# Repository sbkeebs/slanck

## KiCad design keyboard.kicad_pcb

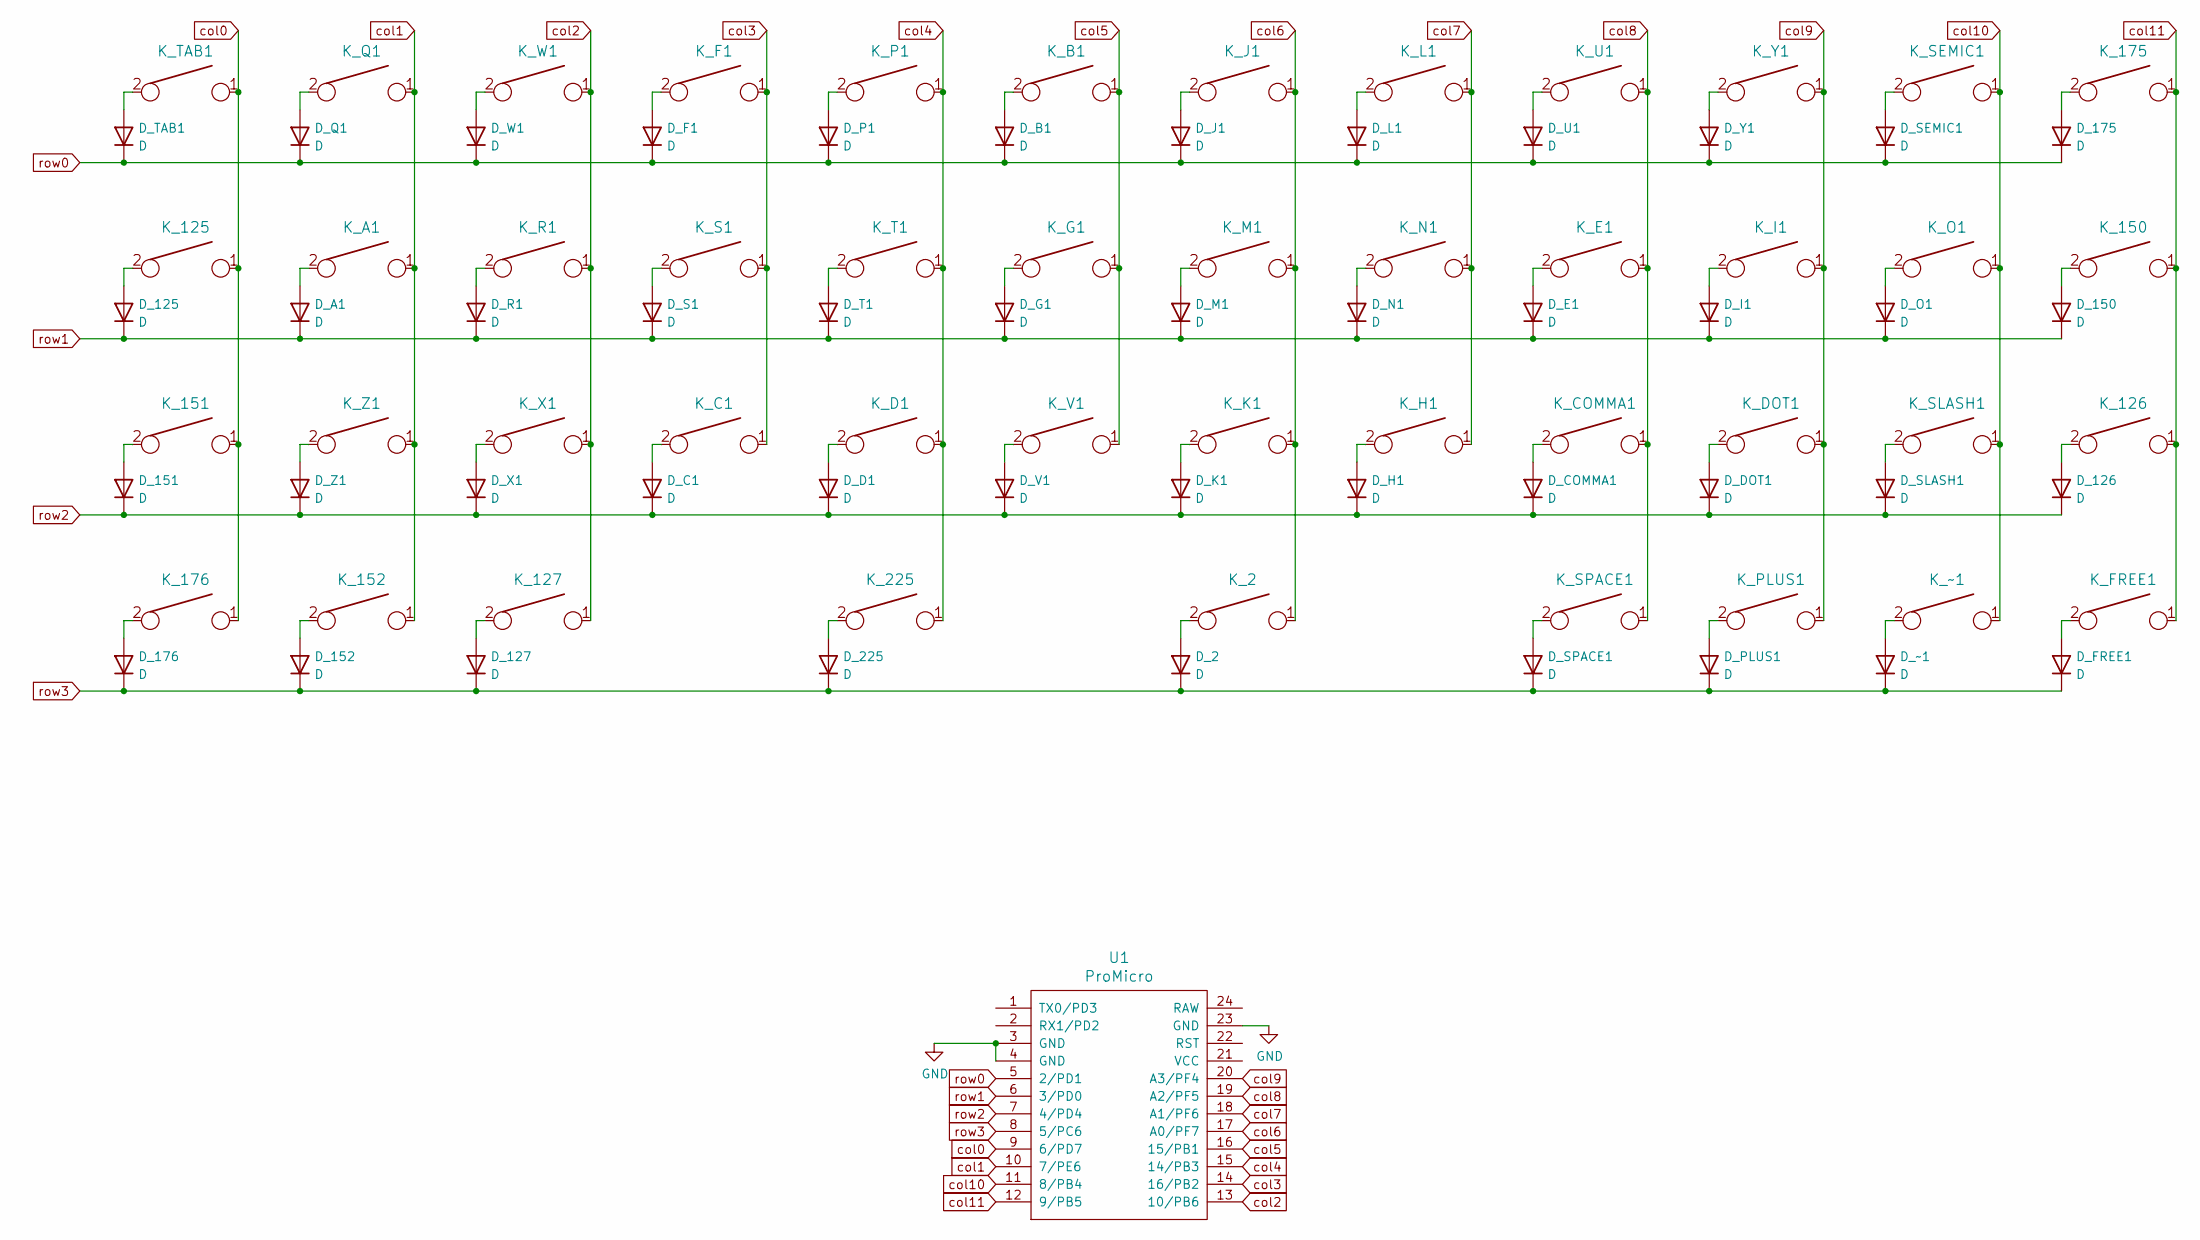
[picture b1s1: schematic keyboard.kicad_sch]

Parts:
D_2, D_125, D_126, D_127, D_150, D_151, D_152, D_175, D_176, D_225: D; D_SOD-123
D_A1: D; D_SOD-123
D_B1: D; D_SOD-123
D_C1: D; D_SOD-123
D_COMMA1: D; D_SOD-123
D_D1: D; D_SOD-123
D_DOT1: D; D_SOD-123
D_E1: D; D_SOD-123
D_F1: D; D_SOD-123
D_FREE1: D; D_SOD-123
D_G1: D; D_SOD-123
D_H1: D; D_SOD-123
D_I1: D; D_SOD-123
D_J1: D; D_SOD-123
D_K1: D; D_SOD-123
D_L1: D; D_SOD-123
D_M1: D; D_SOD-123
D_N1: D; D_SOD-123
D_O1: D; D_SOD-123
D_P1: D; D_SOD-123
D_PLUS1: D; D_SOD-123
D_Q1: D; D_SOD-123
D_R1: D; D_SOD-123
D_S1: D; D_SOD-123
D_SEMIC1: D; D_SOD-123
D_SLASH1: D; D_SOD-123
D_SPACE1: D; D_SOD-123
D_T1: D; D_SOD-123
D_TAB1: D; D_SOD-123
D_U1: D; D_SOD-123
D_V1: D; D_SOD-123
D_W1: D; D_SOD-123
D_X1: D; D_SOD-123
D_Y1: D; D_SOD-123
D_Z1: D; D_SOD-123
D_~1: D; D_SOD-123
K_2: KEYSW; MXOnly-2U-NoLED
K_125, K_126, K_127: KEYSW; MXOnly-1.25U-NoLED
K_150, K_151, K_152: KEYSW; MXOnly-1.5U-NoLED
K_175, K_176: KEYSW; MXOnly-1.75U-NoLED
K_225: KEYSW; MXOnly-2.25U-NoLED
K_A1: KEYSW; MXOnly-1U-NoLED
K_B1: KEYSW; MXOnly-1U-NoLED
K_C1: KEYSW; MXOnly-1U-NoLED
K_COMMA1: KEYSW; MXOnly-1U-NoLED
K_D1: KEYSW; MXOnly-1U-NoLED
K_DOT1: KEYSW; MXOnly-1U-NoLED
K_E1: KEYSW; MXOnly-1U-NoLED
K_F1: KEYSW; MXOnly-1U-NoLED
K_FREE1: KEYSW; MXOnly-1U-NoLED
K_G1: KEYSW; MXOnly-1U-NoLED
K_H1: KEYSW; MXOnly-1U-NoLED
K_I1: KEYSW; MXOnly-1U-NoLED
K_J1: KEYSW; MXOnly-1U-NoLED
K_K1: KEYSW; MXOnly-1U-NoLED
K_L1: KEYSW; MXOnly-1U-NoLED
K_M1: KEYSW; MXOnly-1U-NoLED
K_N1: KEYSW; MXOnly-1U-NoLED
K_O1: KEYSW; MXOnly-1U-NoLED
K_P1: KEYSW; MXOnly-1U-NoLED
K_PLUS1: KEYSW; MXOnly-1U-NoLED
K_Q1: KEYSW; MXOnly-1U-NoLED
K_R1: KEYSW; MXOnly-1U-NoLED
K_S1: KEYSW; MXOnly-1U-NoLED
K_SEMIC1: KEYSW; MXOnly-1U-NoLED
K_SLASH1: KEYSW; MXOnly-1U-NoLED
K_SPACE1: KEYSW; MXOnly-1U-NoLED
K_T1: KEYSW; MXOnly-1U-NoLED
K_TAB1: KEYSW; MXOnly-1U-NoLED
K_U1: KEYSW; MXOnly-1U-NoLED
K_V1: KEYSW; MXOnly-1U-NoLED
K_W1: KEYSW; MXOnly-1U-NoLED
K_X1: KEYSW; MXOnly-1U-NoLED
K_Y1: KEYSW; MXOnly-1U-NoLED
K_Z1: KEYSW; MXOnly-1U-NoLED
K_~1: KEYSW; MXOnly-1U-NoLED
U1: ProMicro; ArduinoProMicro-ZigZag

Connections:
GND: U1.3 (GND), U1.4 (GND), U1.23 (GND)
unnamed: D_2.2 (A), K_2.2
unnamed: D_125.2 (A), K_125.2
unnamed: D_126.2 (A), K_126.2
unnamed: D_127.2 (A), K_127.2
unnamed: D_150.2 (A), K_150.2
unnamed: D_151.2 (A), K_151.2
unnamed: D_152.2 (A), K_152.2
unnamed: D_175.2 (A), K_175.2
unnamed: D_176.2 (A), K_176.2
unnamed: D_225.2 (A), K_225.2
unnamed: D_A1.2 (A), K_A1.2
unnamed: D_B1.2 (A), K_B1.2
unnamed: D_C1.2 (A), K_C1.2
unnamed: D_COMMA1.2 (A), K_COMMA1.2
unnamed: D_D1.2 (A), K_D1.2
unnamed: D_DOT1.2 (A), K_DOT1.2
unnamed: D_E1.2 (A), K_E1.2
unnamed: D_F1.2 (A), K_F1.2
unnamed: D_FREE1.2 (A), K_FREE1.2
unnamed: D_G1.2 (A), K_G1.2
unnamed: D_H1.2 (A), K_H1.2
unnamed: D_I1.2 (A), K_I1.2
unnamed: D_J1.2 (A), K_J1.2
unnamed: D_K1.2 (A), K_K1.2
unnamed: D_L1.2 (A), K_L1.2
unnamed: D_M1.2 (A), K_M1.2
unnamed: D_N1.2 (A), K_N1.2
unnamed: D_O1.2 (A), K_O1.2
unnamed: D_P1.2 (A), K_P1.2
unnamed: D_PLUS1.2 (A), K_PLUS1.2
unnamed: D_Q1.2 (A), K_Q1.2
unnamed: D_R1.2 (A), K_R1.2
unnamed: D_S1.2 (A), K_S1.2
unnamed: D_SEMIC1.2 (A), K_SEMIC1.2
unnamed: D_SLASH1.2 (A), K_SLASH1.2
unnamed: D_SPACE1.2 (A), K_SPACE1.2
unnamed: D_T1.2 (A), K_T1.2
unnamed: D_TAB1.2 (A), K_TAB1.2
unnamed: D_U1.2 (A), K_U1.2
unnamed: D_V1.2 (A), K_V1.2
unnamed: D_W1.2 (A), K_W1.2
unnamed: D_X1.2 (A), K_X1.2
unnamed: D_Y1.2 (A), K_Y1.2
unnamed: D_Z1.2 (A), K_Z1.2
unnamed: D_~1.2 (A), K_~1.2
col0: K_125.1, K_151.1, K_176.1, K_TAB1.1, U1.9 (6/PD7)
col1: K_152.1, K_A1.1, K_Q1.1, K_Z1.1, U1.10 (7/PE6)
col2: K_127.1, K_R1.1, K_W1.1, K_X1.1, U1.13 (10/PB6)
col3: K_C1.1, K_F1.1, K_S1.1, U1.14 (16/PB2)
col4: K_225.1, K_D1.1, K_P1.1, K_T1.1, U1.15 (14/PB3)
col5: K_B1.1, K_G1.1, K_V1.1, U1.16 (15/PB1)
col6: K_2.1, K_J1.1, K_K1.1, K_M1.1, U1.17 (A0/PF7)
col7: K_H1.1, K_L1.1, K_N1.1, U1.18 (A1/PF6)
col8: K_COMMA1.1, K_E1.1, K_SPACE1.1, K_U1.1, U1.19 (A2/PF5)
col9: K_DOT1.1, K_I1.1, K_PLUS1.1, K_Y1.1, U1.20 (A3/PF4)
col10: K_O1.1, K_SEMIC1.1, K_SLASH1.1, K_~1.1, U1.11 (8/PB4); also elsewhere on the board
col11: K_126.1, K_150.1, K_175.1, K_FREE1.1, U1.12 (9/PB5)
row0: D_175.1 (K), D_B1.1 (K), D_F1.1 (K), D_J1.1 (K), D_L1.1 (K), D_P1.1 (K), D_Q1.1 (K), D_SEMIC1.1 (K), D_TAB1.1 (K), D_U1.1 (K), D_W1.1 (K), D_Y1.1 (K), U1.5 (2/PD1)
row1: D_125.1 (K), D_150.1 (K), D_A1.1 (K), D_E1.1 (K), D_G1.1 (K), D_I1.1 (K), D_M1.1 (K), D_N1.1 (K), D_O1.1 (K), D_R1.1 (K), D_S1.1 (K), D_T1.1 (K), U1.6 (3/PD0)
row2: D_126.1 (K), D_151.1 (K), D_C1.1 (K), D_COMMA1.1 (K), D_D1.1 (K), D_DOT1.1 (K), D_H1.1 (K), D_K1.1 (K), D_SLASH1.1 (K), D_V1.1 (K), D_X1.1 (K), D_Z1.1 (K), U1.7 (4/PD4)
row3: D_2.1 (K), D_127.1 (K), D_152.1 (K), D_176.1 (K), D_225.1 (K), D_FREE1.1 (K), D_PLUS1.1 (K), D_SPACE1.1 (K), D_~1.1 (K), U1.8 (5/PC6); also elsewhere on the board

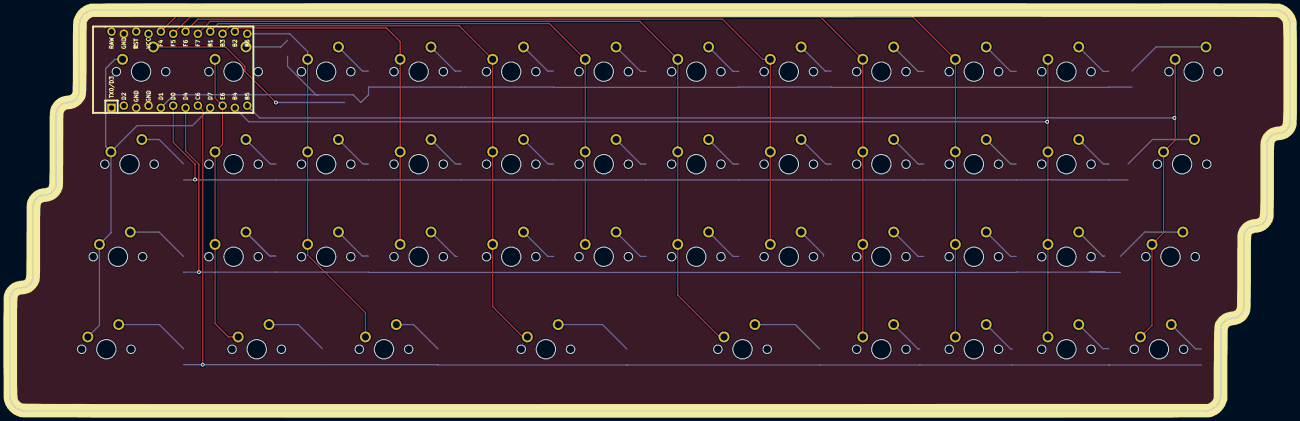
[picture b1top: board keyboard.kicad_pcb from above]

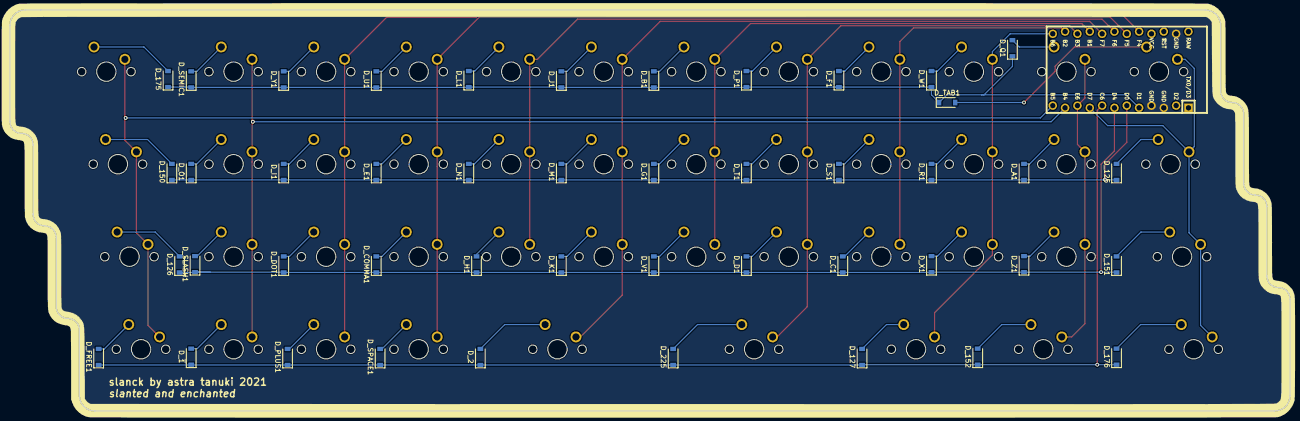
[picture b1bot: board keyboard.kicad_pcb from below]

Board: 2 copper layers, 263.5 x 82.5 mm, 91 parts (45 on the bottom side), 62 nets.

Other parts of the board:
D_~{1}: D; D_SOD-123
K_~{1}: KEYSW; MXOnly-1U-NoLED

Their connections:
unnamed: D_~{1}.2, K_~{1}.2
col10: K_~{1}.1; also elsewhere on the board
row3: D_~{1}.1; also elsewhere on the board

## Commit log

2023-01-09 Add license file
2023-01-09 Keyboard layout in KLE raw data
